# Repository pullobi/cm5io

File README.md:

## custom carrier board for the CM5
used [Raspberry Pi's official design files for the CM5 IO board](https://pip.raspberrypi.com/categories/1098-design-files)

# other
Some of the 3d models need to be downloaded form the following places and put into the CM5IO.3shapes directory some models are approximations.

https://datasheets.raspberrypi.org/cm5/CM5-step.zip
https://www.molex.com/molex/products/part-detail/memory_card_socket/5033981892

The models provided in the 3dmodels directory are from various manufacturers including Diodes, Hirose, MTCONN, Toby, TRXCOM. Terms and conditions for the use of the models remain with the original manufacture.

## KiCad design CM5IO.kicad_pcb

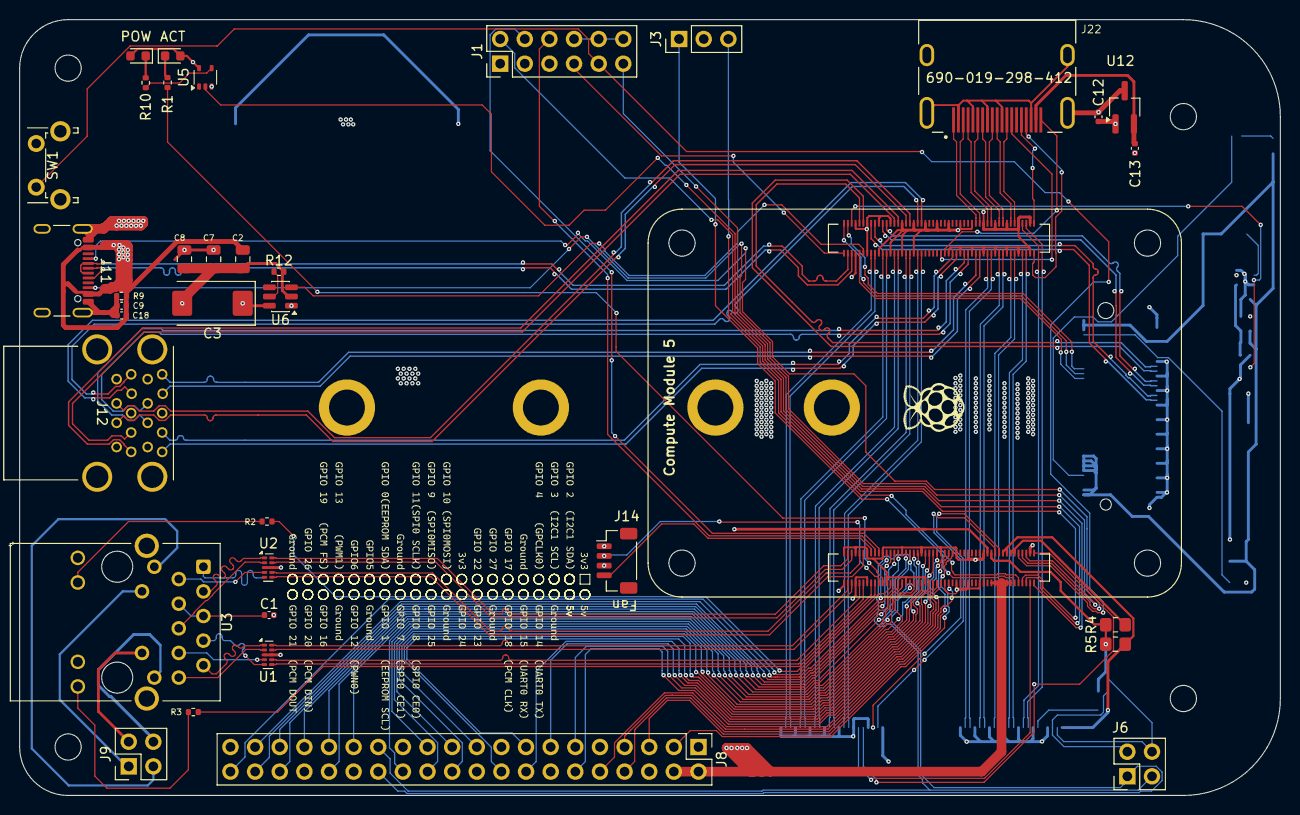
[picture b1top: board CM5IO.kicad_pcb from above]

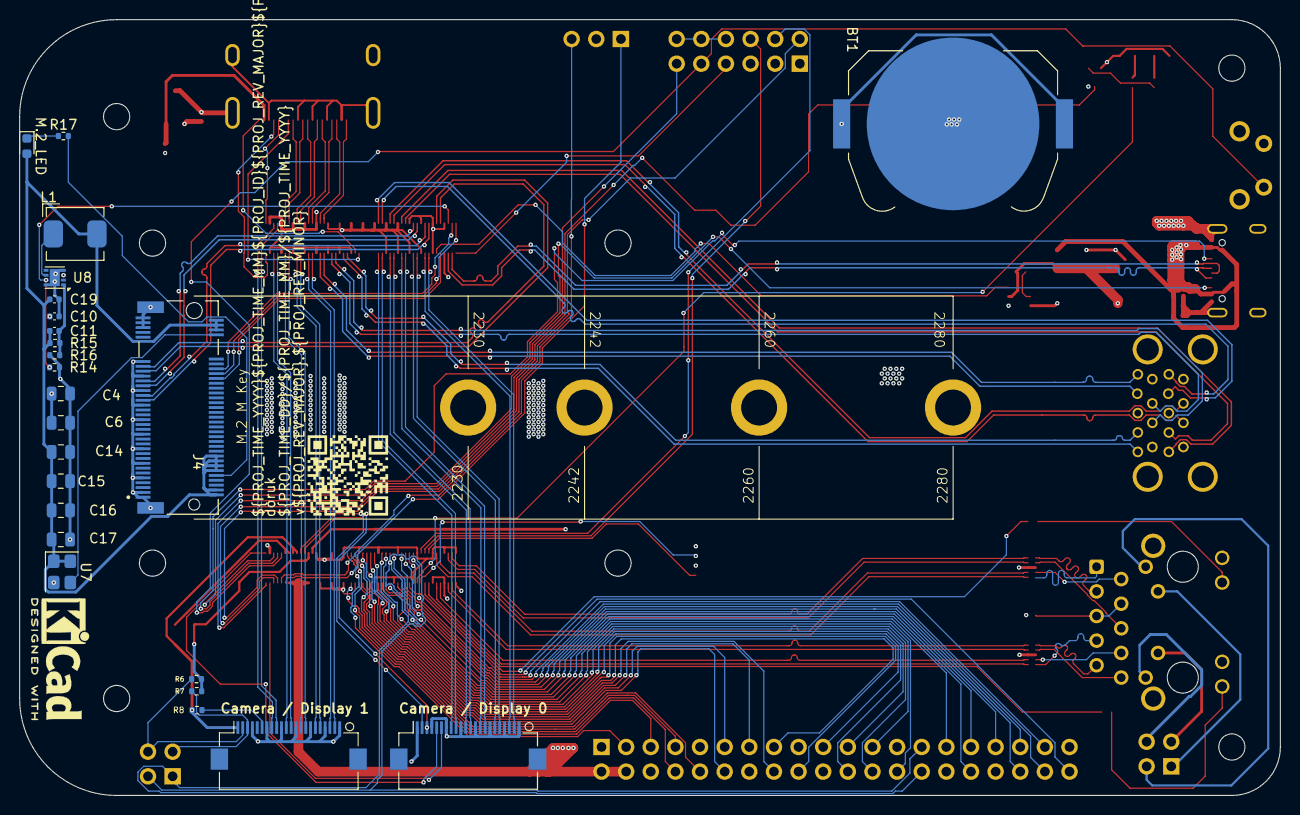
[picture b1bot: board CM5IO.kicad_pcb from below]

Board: 4 copper layers, 130.0 x 80.0 mm, 65 parts (25 on the bottom side), 141 nets.

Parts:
ACT: LED Green; LED_0603_1608Metric
BT1: Battery_Cell; BatteryHolder_Keystone_3034_1x20mm
C1, C9, C10, C12, C13, C18, C19: 100n; C_0402_1005Metric
C2, C4, C6, C7, C8, C14, C15, C16, C17: 10u; C_0805_2012Metric
C3: 100uF; CP_EIA-7343-31_Kemet-D
C11: 4.7nF; C_0402_1005Metric
Compute Module 5: ComputeModule5-CM5; Raspberry-Pi-5-Compute-Module
H1, H2, H3, H4: MountingHole; MountingHole_2.7mm_M2.5_DIN965
J1: Conn_02x06_Top_Bottom; PinHeader_2x06_P2.54mm_Vertical
J3: Conn_01x03; PinHeader_1x03_P2.54mm_Vertical
J4: Bus_M.2_Socket_M; M.2 M Key socket
J5, J16: Conn_01x22_Female; Hirose_FH12-22S-0.5SH_1x22-1MP_P0.50mm_Horizontal
J6, J9: THD-02-R; PinHeader_2x02_P2.54mm_Vertical
J8: THD-20-R; PinHeader_2x20_P2.54mm_Vertical
J11: USB_C_Receptacle_USB2.0; USB_C_Receptacle_GCT_USB4105-xx-A_16P_TopMnt_Horizontal
J12: USB3_A; MTCONN_UBAF30-D2011
J14: JST_SHBM04B-SRSS-TB; JST_SH_BM04B-SRSS-TB_1x04-1MP_P1.00mm_Vertical
J22: 690-019-298-412; EDAC 690-019-298-412
L1: 2.2uH; L_Bourns_SRP5030CC
M.2_LED: LED Green; LED_0603_1608Metric
POW: LED Red; LED_0603_1608Metric
R1, R10, R17: 1k; R_0402_1005Metric
R2, R3: 470R; R_0402_1005Metric
R4: nf; R_0805_2012Metric_Pad1.20x1.40mm_HandSolder
R5: 0R; R_0805_2012Metric_Pad1.20x1.40mm_HandSolder
R6, R7, R8, R9, R16: 2.2K 1%; R_0402_1005Metric
R12: 15K 1%; R_0402_1005Metric
R14: 100K 1%; R_0402_1005Metric
R15: 10K 1%; R_0402_1005Metric
SW1: Right angle Tact button; SW_Tactile_SPST_Angled_PTS645Vx58-2LFS
U1, U2: TPD4EUSB30; USON-10_2.5x1.0mm_P0.5mm
U3: MagJack-A70-112-331N126; TRJG0926HENL
U5: 74LVC1G07SE-7; SOT-353_SC-70-5
U6: AP22653W6; SOT-23-6
U7: ASEK-32.768KHZ-L-R-T; Crystal_SMD_3225-4Pin_3.2x2.5mm
U8: AP3441SHE-7B; DFN-8-1EP_2x2mm_P0.5mm_EP1.05x1.75mm
U12: RT9742SNGV; TSOT-23_HandSoldering
logo1: KiCad-Logo2_5mm_SilkScreen

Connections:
/+3.3v: ACT.2 (A), Compute Module 5.84 (+3.3v_(Output)), Compute Module 5.86 (+3.3v_(Output)), J5.22, J8.1, J8.17, J16.22, POW.2 (A), R5.1, R8.1, U3.15 (LEDY_A), U3.17 (LEDG_A), U5.5 (VCC)
/+5v: C2.1, C4.1, C6.1, C9.1, C10.1, C12.1, C18.1, Compute Module 5.77 (+5v_(Input)), Compute Module 5.79 (+5v_(Input)), Compute Module 5.81 (+5v_(Input)), Compute Module 5.83 (+5v_(Input)), Compute Module 5.85 (+5v_(Input)), Compute Module 5.87 (+5v_(Input)), J8.2, J8.4, J11.A4 (VBUS), J11.A9 (VBUS), J11.B4 (VBUS), J11.B9 (VBUS), J14.1, R9.1, U6.1 (IN), U8.3 (VIN), U12.1 (IN)
/CC1: Compute Module 5.94 (CC1), J11.A5 (CC1)
/CC2: Compute Module 5.96 (CC2), J11.B5 (CC2)
/CM5_GPIO ( Ethernet, GPIO, SDCARD)/+1.8v: Compute Module 5.88 (+1.8v_(Output)), Compute Module 5.90 (+1.8v_(Output)), R4.1
/CM5_GPIO ( Ethernet, GPIO, SDCARD)/BT_nDis: Compute Module 5.91 (BT_nDisable), J3.3
/CM5_GPIO ( Ethernet, GPIO, SDCARD)/CAM_GPIO0: Compute Module 5.97 (CAM_GPIO0), J5.17
/CM5_GPIO ( Ethernet, GPIO, SDCARD)/CAM_GPIO1: Compute Module 5.100 (CAM_GPIO1), J5.18
/CM5_GPIO ( Ethernet, GPIO, SDCARD)/EEPROM_nWP: Compute Module 5.20 (EEPROM_nWP), J1.4
/CM5_GPIO ( Ethernet, GPIO, SDCARD)/ETH_LEDG: Compute Module 5.17 (Ethernet_nLED2(3.3v)), R2.2
/CM5_GPIO ( Ethernet, GPIO, SDCARD)/ETH_LEDY: Compute Module 5.15 (Ethernet_nLED3(3.3v)), R3.2
/CM5_GPIO ( Ethernet, GPIO, SDCARD)/GPIO2: Compute Module 5.58 (GPIO2), J8.3
/CM5_GPIO ( Ethernet, GPIO, SDCARD)/GPIO3: Compute Module 5.56 (GPIO3), J8.5
/CM5_GPIO ( Ethernet, GPIO, SDCARD)/GPIO4: Compute Module 5.54 (GPIO4), J8.7
/CM5_GPIO ( Ethernet, GPIO, SDCARD)/GPIO5: Compute Module 5.34 (GPIO5), J8.29
/CM5_GPIO ( Ethernet, GPIO, SDCARD)/GPIO6: Compute Module 5.30 (GPIO6), J8.31
/CM5_GPIO ( Ethernet, GPIO, SDCARD)/GPIO7: Compute Module 5.37 (GPIO7), J8.26
/CM5_GPIO ( Ethernet, GPIO, SDCARD)/GPIO8: Compute Module 5.39 (GPIO8), J8.24
/CM5_GPIO ( Ethernet, GPIO, SDCARD)/GPIO9: Compute Module 5.40 (GPIO9), J8.21
/CM5_GPIO ( Ethernet, GPIO, SDCARD)/GPIO10: Compute Module 5.44 (GPIO10), J8.19
/CM5_GPIO ( Ethernet, GPIO, SDCARD)/GPIO11: Compute Module 5.38 (GPIO11), J8.23
/CM5_GPIO ( Ethernet, GPIO, SDCARD)/GPIO12: Compute Module 5.31 (GPIO12), J8.32
/CM5_GPIO ( Ethernet, GPIO, SDCARD)/GPIO13: Compute Module 5.28 (GPIO13), J8.33
/CM5_GPIO ( Ethernet, GPIO, SDCARD)/GPIO14: Compute Module 5.55 (GPIO14), J8.8
/CM5_GPIO ( Ethernet, GPIO, SDCARD)/GPIO15: Compute Module 5.51 (GPIO15), J8.10
/CM5_GPIO ( Ethernet, GPIO, SDCARD)/GPIO16: Compute Module 5.29 (GPIO16), J8.36
/CM5_GPIO ( Ethernet, GPIO, SDCARD)/GPIO17: Compute Module 5.50 (GPIO17), J8.11
/CM5_GPIO ( Ethernet, GPIO, SDCARD)/GPIO18: Compute Module 5.49 (GPIO18), J8.12
/CM5_GPIO ( Ethernet, GPIO, SDCARD)/GPIO19: Compute Module 5.26 (GPIO19), J8.35
/CM5_GPIO ( Ethernet, GPIO, SDCARD)/GPIO20: Compute Module 5.27 (GPIO20), J8.38
/CM5_GPIO ( Ethernet, GPIO, SDCARD)/GPIO21: Compute Module 5.25 (GPIO21), J8.40
/CM5_GPIO ( Ethernet, GPIO, SDCARD)/GPIO22: Compute Module 5.46 (GPIO22), J8.15
/CM5_GPIO ( Ethernet, GPIO, SDCARD)/GPIO23: Compute Module 5.47 (GPIO23), J8.16
/CM5_GPIO ( Ethernet, GPIO, SDCARD)/GPIO24: Compute Module 5.45 (GPIO24), J8.18
/CM5_GPIO ( Ethernet, GPIO, SDCARD)/GPIO25: Compute Module 5.41 (GPIO25), J8.22
/CM5_GPIO ( Ethernet, GPIO, SDCARD)/GPIO26: Compute Module 5.24 (GPIO26), J8.37
/CM5_GPIO ( Ethernet, GPIO, SDCARD)/GPIO27: Compute Module 5.48 (GPIO27), J8.13
/CM5_GPIO ( Ethernet, GPIO, SDCARD)/GPIO_VREF: Compute Module 5.78 (GPIO_VREF(1.8v/3.3v_Input)), R4.2, R5.2, R6.1, R7.1
/CM5_GPIO ( Ethernet, GPIO, SDCARD)/ID_SC: Compute Module 5.35 (ID_SC), J6.1, J8.28
/CM5_GPIO ( Ethernet, GPIO, SDCARD)/ID_SD: Compute Module 5.36 (ID_SD), J6.3, J8.27
/CM5_GPIO ( Ethernet, GPIO, SDCARD)/PMIC_ENABLE: Compute Module 5.99 (PMIC_ENABLE), J1.11
/CM5_GPIO ( Ethernet, GPIO, SDCARD)/PWM: Compute Module 5.19 (FAN_PWM), J14.2
/CM5_GPIO ( Ethernet, GPIO, SDCARD)/PWR_BUT: Compute Module 5.92 (PWR_BUT), J1.9, SW1.1
/CM5_GPIO ( Ethernet, GPIO, SDCARD)/SYNC_OUT: Compute Module 5.18 (Ethernet_SYNC_OUT(3.3v)), J1.6
/CM5_GPIO ( Ethernet, GPIO, SDCARD)/TACHO: Compute Module 5.16 (FAN_TACHO), J14.4
/CM5_GPIO ( Ethernet, GPIO, SDCARD)/TR0_TAP: J9.3, U3.11 (VC1)
/CM5_GPIO ( Ethernet, GPIO, SDCARD)/TR1_TAP: J9.1, U3.12 (VC2)
/CM5_GPIO ( Ethernet, GPIO, SDCARD)/TR2_TAP: J9.2, U3.13 (VC3)
/CM5_GPIO ( Ethernet, GPIO, SDCARD)/TR3_TAP: J9.4, U3.14 (VC4)
/CM5_GPIO ( Ethernet, GPIO, SDCARD)/TRD0_N: Compute Module 5.10 (Ethernet_Pair0_N), U2.4 (D2+), U2.7, U3.2 (TRD0-)
/CM5_GPIO ( Ethernet, GPIO, SDCARD)/TRD0_P: Compute Module 5.12 (Ethernet_Pair0_P), U2.5 (D2-), U2.6, U3.1 (TRD0+)
/CM5_GPIO ( Ethernet, GPIO, SDCARD)/TRD1_N: Compute Module 5.6 (Ethernet_Pair1_N), U2.2 (D1-), U2.9, U3.6 (TRD1-)
/CM5_GPIO ( Ethernet, GPIO, SDCARD)/TRD1_P: Compute Module 5.4 (Ethernet_Pair1_P), U2.1 (D1+), U2.10, U3.3 (TRD1+)
/CM5_GPIO ( Ethernet, GPIO, SDCARD)/TRD2_N: Compute Module 5.9 (Ethernet_Pair2_N), U1.4 (D2+), U1.7, U3.8 (TRD2-)
/CM5_GPIO ( Ethernet, GPIO, SDCARD)/TRD2_P: Compute Module 5.11 (Ethernet_Pair2_P), U1.5 (D2-), U1.6, U3.7 (TRD2+)
/CM5_GPIO ( Ethernet, GPIO, SDCARD)/TRD3_N: Compute Module 5.5 (Ethernet_Pair3_N), U1.2 (D1-), U1.9, U3.10 (TRD3-)
/CM5_GPIO ( Ethernet, GPIO, SDCARD)/TRD3_P: Compute Module 5.3 (Ethernet_Pair3_P), U1.1 (D1+), U1.10, U3.9 (TRD3+)
/CM5_GPIO ( Ethernet, GPIO, SDCARD)/USBOTG: Compute Module 5.101 (USB_OTG_ID), J1.7
/CM5_GPIO ( Ethernet, GPIO, SDCARD)/VBAT: BT1.1 (+), Compute Module 5.76 (VBAT)
/CM5_GPIO ( Ethernet, GPIO, SDCARD)/WL_nDis: Compute Module 5.89 (WiFi_nDisable), J3.1
/CM5_GPIO ( Ethernet, GPIO, SDCARD)/nPWR_LED: Compute Module 5.95 (LED_nPWR), U5.2
/CM5_GPIO ( Ethernet, GPIO, SDCARD)/nRPIBOOT: Compute Module 5.93 (nRPIBOOT), J1.2
/CM5_HighSpeed/DPHY0_C_N: Compute Module 5.127 (MIPI0_C_N), J5.8
/CM5_HighSpeed/DPHY0_C_P: Compute Module 5.129 (MIPI0_C_P), J5.9
/CM5_HighSpeed/DPHY0_D0_N: Compute Module 5.115 (MIPI0_D0_N), J5.2
/CM5_HighSpeed/DPHY0_D0_P: Compute Module 5.117 (MIPI0_D0_P), J5.3
/CM5_HighSpeed/DPHY0_D1_N: Compute Module 5.121 (MIPI0_D1_N), J5.5
/CM5_HighSpeed/DPHY0_D1_P: Compute Module 5.123 (MIPI0_D1_P), J5.6
/CM5_HighSpeed/DPHY0_D2_N: Compute Module 5.133 (MIPI0_D2_N), J5.11
/CM5_HighSpeed/DPHY0_D2_P: Compute Module 5.135 (MIPI0_D2_P), J5.12
/CM5_HighSpeed/DPHY0_D3_N: Compute Module 5.139 (MIPI0_D3_N), J5.14
/CM5_HighSpeed/DPHY0_D3_P: Compute Module 5.141 (MIPI0_D3_P), J5.15
/CM5_HighSpeed/DPHY1_C_N: Compute Module 5.187 (MIPI1_C_N), J16.8
/CM5_HighSpeed/DPHY1_C_P: Compute Module 5.189 (MIPI1_C_P), J16.9
/CM5_HighSpeed/DPHY1_D0_N: Compute Module 5.175 (MIPI1_D0_N), J16.2
/CM5_HighSpeed/DPHY1_D0_P: Compute Module 5.177 (MIPI1_D0_P), J16.3
/CM5_HighSpeed/DPHY1_D1_N: Compute Module 5.181 (MIPI1_D1_N), J16.5
/CM5_HighSpeed/DPHY1_D1_P: Compute Module 5.183 (MIPI1_D1_P), J16.6
/CM5_HighSpeed/DPHY1_D2_N: Compute Module 5.193 (MIPI1_D2_N), J16.11
/CM5_HighSpeed/DPHY1_D2_P: Compute Module 5.195 (MIPI1_D2_P), J16.12
/CM5_HighSpeed/DPHY1_D3_N: Compute Module 5.194 (MIPI1_D3_N), J16.14
/CM5_HighSpeed/DPHY1_D3_P: Compute Module 5.196 (MIPI1_D3_P), J16.15
/CM5_HighSpeed/HDMI0_CEC: Compute Module 5.151 (HDMI0_CEC), J22.13 (CEC)
/CM5_HighSpeed/HDMI0_CK_N: Compute Module 5.190 (HDMI0_CLK_N), J22.12 (CK-)
/CM5_HighSpeed/HDMI0_CK_P: Compute Module 5.188 (HDMI0_CLK_P), J22.10 (CK+)
/CM5_HighSpeed/HDMI0_D0_N: Compute Module 5.184 (HDMI0_TX0_N), J22.9 (D0-)
/CM5_HighSpeed/HDMI0_D0_P: Compute Module 5.182 (HDMI0_TX0_P), J22.7 (D0+)
/CM5_HighSpeed/HDMI0_D1_N: Compute Module 5.178 (HDMI0_TX1_N), J22.6 (D1-)
/CM5_HighSpeed/HDMI0_D1_P: Compute Module 5.176 (HDMI0_TX1_P), J22.4 (D1+)
/CM5_HighSpeed/HDMI0_D2_N: Compute Module 5.172 (HDMI0_TX2_N), J22.3 (D2-)
/CM5_HighSpeed/HDMI0_D2_P: Compute Module 5.170 (HDMI0_TX2_P), J22.1 (D2+)
/CM5_HighSpeed/HDMI0_HOTPLUG: Compute Module 5.153 (HDMI0_HOTPLUG), J22.19 (HPD/HEAC-)
/CM5_HighSpeed/HDMI0_SCL: Compute Module 5.200 (HDMI0_SCL), J22.15 (SCL)
/CM5_HighSpeed/HDMI0_SDA: Compute Module 5.199 (HDMI0_SDA), J22.16 (SDA)
/CM5_HighSpeed/HDMI_5v: C13.1, J22.18 (+5V), U12.2 (OUT)
/CM5_HighSpeed/PCIE_CLK_N: Compute Module 5.112 (PCIe_CLK_N), J4.53 (REFCLKn)
/CM5_HighSpeed/PCIE_CLK_P: Compute Module 5.110 (PCIe_CLK_P), J4.55 (REFCLKp)
/CM5_HighSpeed/PCIE_PWR_EN: Compute Module 5.106 (PCIE_PWR_EN), R14.1, U8.7 (EN)
/CM5_HighSpeed/PCIE_RX_N: Compute Module 5.118 (PCIe_RX_N), J4.43 (PETp0)
/CM5_HighSpeed/PCIE_RX_P: Compute Module 5.116 (PCIe_RX_P), J4.41 (PETn0)
/CM5_HighSpeed/PCIE_TX_N: Compute Module 5.124 (PCIe_TX_N), J4.49 (PERp0)
/CM5_HighSpeed/PCIE_TX_P: Compute Module 5.122 (PCIe_TX_P), J4.47 (PERn0)
/CM5_HighSpeed/PCIE_nCLKREQ: Compute Module 5.102 (PCIe_nCLKREQ), J4.52 (~CLKREQ)
/CM5_HighSpeed/PCIE_nRST: Compute Module 5.109 (PCIe_nRST), J4.50 (~PERST)
/CM5_HighSpeed/PCIE_nWAKE: Compute Module 5.104 (PCIE_nWAKE), J4.54 (~PEWAKE)
/CM5_HighSpeed/SCL0: Compute Module 5.80 (SCL0), J5.20
/CM5_HighSpeed/SCL1: J6.2, J16.20, R7.2
/CM5_HighSpeed/SDA0: Compute Module 5.82 (SDA0), J5.21
/CM5_HighSpeed/SDA1: J6.4, J16.21, R6.2
/CM5_HighSpeed/USB3-0-D_N: Compute Module 5.136 (USB3-0-D_N), J12.A2 (D-)
/CM5_HighSpeed/USB3-0-D_P: Compute Module 5.134 (USB3-0-D_P), J12.A3 (D+)
/CM5_HighSpeed/USB3-0-RX_N: Compute Module 5.128 (USB3-0-RX_N), J12.A6 (SSRX+)
/CM5_HighSpeed/USB3-0-RX_P: Compute Module 5.130 (USB3-0-RX_P), J12.A5 (SSRX-)
/CM5_HighSpeed/USB3-0-TX_N: Compute Module 5.140 (USB3-0-TX_N), J12.A9 (SSTX+)
/CM5_HighSpeed/USB3-0-TX_P: Compute Module 5.142 (USB3-0-TX_P), J12.A8 (SSTX-)
/CM5_HighSpeed/USB3-1-D_N: Compute Module 5.165 (USB3-1-D_N), J12.B2 (D-)
/CM5_HighSpeed/USB3-1-D_P: Compute Module 5.163 (USB3-1-D_P), J12.B3 (D+)
/CM5_HighSpeed/USB3-1-RX_N: Compute Module 5.157 (USB3-1-RX_N), J12.B6 (SSRX+)
/CM5_HighSpeed/USB3-1-RX_P: Compute Module 5.159 (USB3-1-RX_P), J12.B5 (SSRX-)
/CM5_HighSpeed/USB3-1-TX_N: Compute Module 5.169 (USB3-1-TX_N), J12.B9 (SSTX+)
/CM5_HighSpeed/USB3-1-TX_P: Compute Module 5.171 (USB3-1-TX_P), J12.B8 (SSTX-)
/CM5_HighSpeed/VBUS: C3.1, C7.1, C8.1, J12.A1 (VBUS), J12.B1 (VBUS), U6.6 (OUT)
/CM5_HighSpeed/VBUS_EN: Compute Module 5.111 (VBUS_EN), U6.3 (EN)
/PCIe-M2/FB: C11.2, R15.2, R16.1, U8.1 (FB)
/PCIe-M2/M2_3v3: C11.1, C14.1, C15.1, C16.1, C17.1, C19.1, J4.2 (3.3V), J4.4 (3.3V), J4.12 (3.3V), J4.14 (3.3V), J4.16 (3.3V), J4.18 (3.3V), J4.70 (3.3V), J4.72 (3.3V), J4.74 (3.3V), L1.2, M.2_LED.2 (A), R15.1, U7.1 (EN), U7.4 (VDD)
/USB2_N: Compute Module 5.103 (USB2_N), J11.A7 (D-), J11.B7 (D-)
/USB2_P: Compute Module 5.105 (USB2_P), J11.A6 (D+), J11.B6 (D+)
GND: BT1.2 (-), C1.2, C2.2, C3.2, C4.2, C6.2, C7.2, C8.2, C9.2, C10.2, C12.2, C13.2, C14.2, C15.2, C16.2, C17.2, C18.2, C19.2, Compute Module 5.1 (GND), Compute Module 5.2 (GND), Compute Module 5.7 (GND), Compute Module 5.8 (GND), Compute Module 5.13 (GND), Compute Module 5.14 (GND), Compute Module 5.22 (GND), Compute Module 5.23 (GND), Compute Module 5.32 (GND), Compute Module 5.33 (GND), Compute Module 5.42 (GND), Compute Module 5.43 (GND), Compute Module 5.52 (GND), Compute Module 5.53 (GND), Compute Module 5.59 (GND), Compute Module 5.60 (GND), Compute Module 5.65 (GND), Compute Module 5.66 (GND), Compute Module 5.71 (GND), Compute Module 5.74 (GND), Compute Module 5.98 (GND), Compute Module 5.107 (GND), Compute Module 5.108 (GND), Compute Module 5.113 (GND), Compute Module 5.114 (GND), Compute Module 5.119 (GND), Compute Module 5.120 (GND), Compute Module 5.125 (GND), Compute Module 5.126 (GND), Compute Module 5.131 (GND), Compute Module 5.132 (GND), Compute Module 5.137 (GND), Compute Module 5.138 (GND), Compute Module 5.144 (GND), Compute Module 5.150 (GND), Compute Module 5.155 (GND), Compute Module 5.156 (GND), Compute Module 5.161 (GND), Compute Module 5.162 (GND), Compute Module 5.167 (GND), Compute Module 5.168 (GND), Compute Module 5.173 (GND), Compute Module 5.174 (GND), Compute Module 5.179 (GND), Compute Module 5.180 (GND), Compute Module 5.185 (GND), Compute Module 5.186 (GND), Compute Module 5.191 (GND), Compute Module 5.192 (GND), Compute Module 5.197 (GND), Compute Module 5.198 (GND), J1.1, J1.3, J1.5, J1.8, J1.10, J1.12, J3.2, J4.1 (GND), J4.3 (GND), J4.9 (GND), J4.15 (GND), J4.21 (GND), J4.27 (GND), J4.33 (GND), J4.39 (GND), J4.45 (GND), J4.51 (GND), J4.57 (GND), J4.71 (GND), J4.73 (GND), J4.75 (GND), J4.M1 (GND2230), J4.M2 (GND2242), J4.M3 (GND2260), J4.M4 (GND2280), J4.S1, J4.S2, J5.1, J5.4, J5.7, J5.10, J5.13, J5.16, J5.19, J8.6, J8.9, J8.14, J8.20, J8.25, J8.30, J8.34, J8.39, J11.A1 (GND), J11.A12 (GND), J11.B1 (GND), J11.B12 (GND), J11.S1 (SHIELD), J12.10 (SHIELD), J12.A4 (GND), J12.A7 (DRAIN), J12.B4 (GND), J12.B7 (DRAIN), J14.3, J16.1, J16.4, J16.7, J16.10, J16.13, J16.16, J16.19, J22.2 (D2S), J22.5 (D1S), J22.8 (D0S), J22.11 (CKS), J22.17 (GND), J22.SH1 (SH), J22.SH2 (SH), J22.SH3 (SH), J22.SH4 (SH), R9.2, R12.2, R14.2, R16.2, SW1.2, U1.3 (GND), U1.8 (GND), U2.3 (GND), U2.8 (GND), U3.19 (SHIELD), U3.20 (SHIELD), U5.3 (GND), U6.2 (GND), U7.2 (GND), U8.4 (PGND), U8.8 (SGND), U8.9 (PAD), U12.3 (GND)
unnamed: C1.1, U3.4 (CT), U3.5 (CT)
unnamed: POW.1 (K), R10.1
unnamed: ACT.1 (K), R1.1
unnamed: M.2_LED.1 (K), R17.1
unnamed: J4.10 (DAS/~DSS/~LED1), R17.2
unnamed: J4.68 (SUSCLK), U7.3 (Out)
unnamed: J16.17, R8.2
unnamed: Compute Module 5.21 (LED_nACT), R1.2
unnamed: R10.2, U5.4
unnamed: R3.1, U3.18 (LEDG_K)
unnamed: R2.1, U3.16 (LEDY_K)
unnamed: R12.1, U6.5 (ILIM)
unnamed: L1.1, U8.6 (LX)

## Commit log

2025-11-29 Tuning for high speed lanes, thicker voltage/ground traces, add missing 3d model for fan connector.
2025-11-29 Added model for Fan connector (JST_SH_BM04B-SRSS-TB_1x04-1MP_P1.00mm_Vertical) Thickened power and voltage lines Tuned all high speed lines for skew
2025-11-29 Tuned length on high speed signals Added PoE Taps Thickened voltage traces Added fan connector model
2025-12-04 redesigned board with 4 layers
2025-12-04 fixed 3d model of a JST connector
2025-12-07 added credentials and GPIO pinout silkscreen graphics, improvements on various stuff
2025-12-07 update version
